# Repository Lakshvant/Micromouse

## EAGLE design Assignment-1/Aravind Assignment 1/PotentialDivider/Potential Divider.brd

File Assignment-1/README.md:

# Micromouse Assignment 1
Robotics Club , SNT ,  IITK 

All the mentees are requested to make a schematic file and a pcb file for these 4 circuits.
* Potential divider
* Astable multivibrator 
* Wheatstone bridge
* Diode as voltage regulator

## Submission Format
In the Assignment-1 folder of the repo make a folder in your name containing the 
files and make a pull request when your are done
 
### Note :
You will need to fork the repo before making any changes in it.\
Contact mentors if facing any issues.

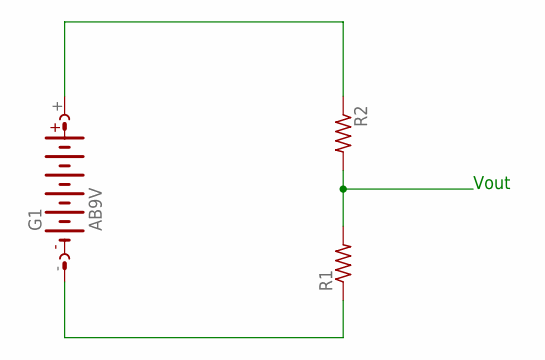
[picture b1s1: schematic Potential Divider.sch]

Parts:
G1: AB9V
R1, R2: R-US_R0805; R0805

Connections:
unnamed: G1.+, R2.1
unnamed: R1.2, R2.2
unnamed: G1.-, R1.1

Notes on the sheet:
Vout

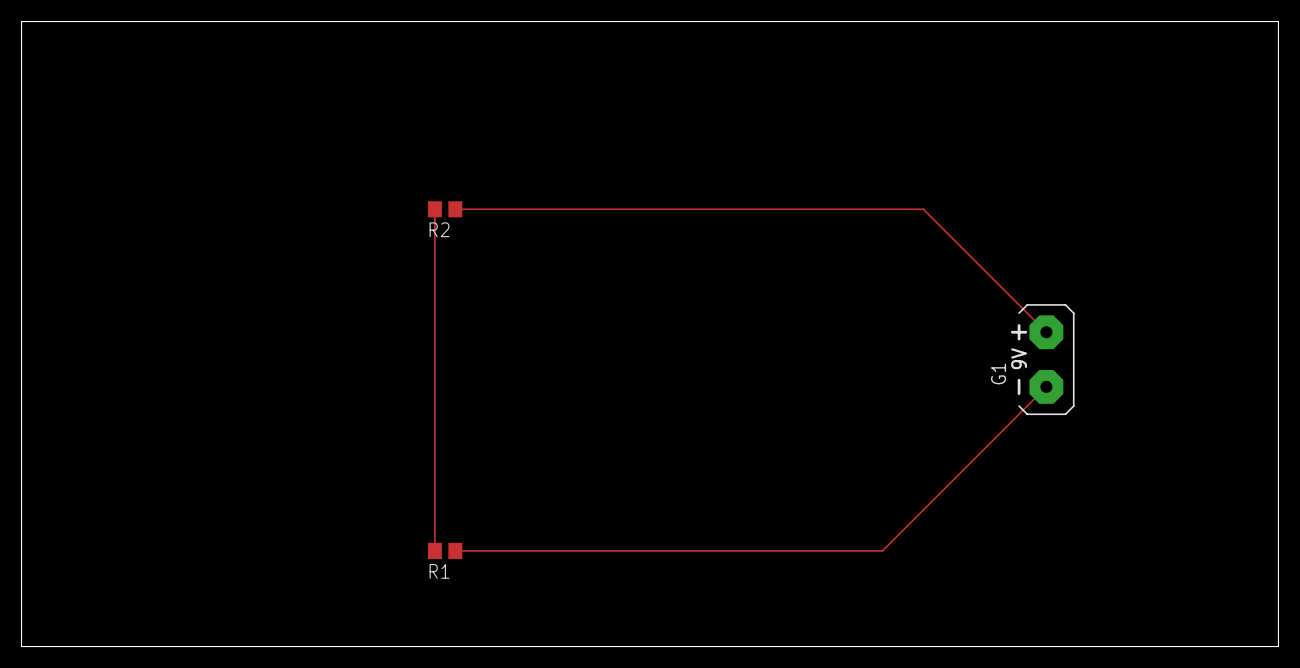
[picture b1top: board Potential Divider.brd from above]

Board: 2 copper layers, 116.8 x 58.1 mm, 3 parts (0 on the bottom side), 3 nets.

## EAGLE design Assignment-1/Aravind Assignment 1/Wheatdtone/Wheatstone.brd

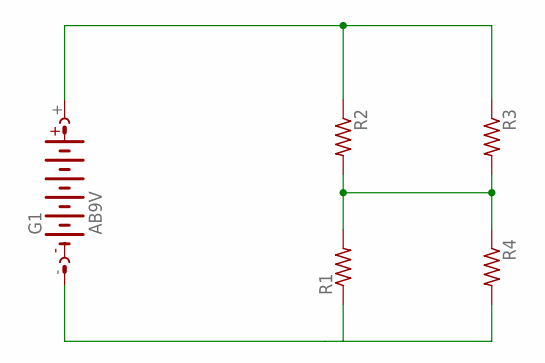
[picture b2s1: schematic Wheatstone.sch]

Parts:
G1: AB9V
R1, R2, R3, R4: R-US_R0805; R0805

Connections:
unnamed: G1.+, R2.1, R3.1
unnamed: R1.2, R2.2, R3.2, R4.1
unnamed: G1.-, R1.1, R4.2

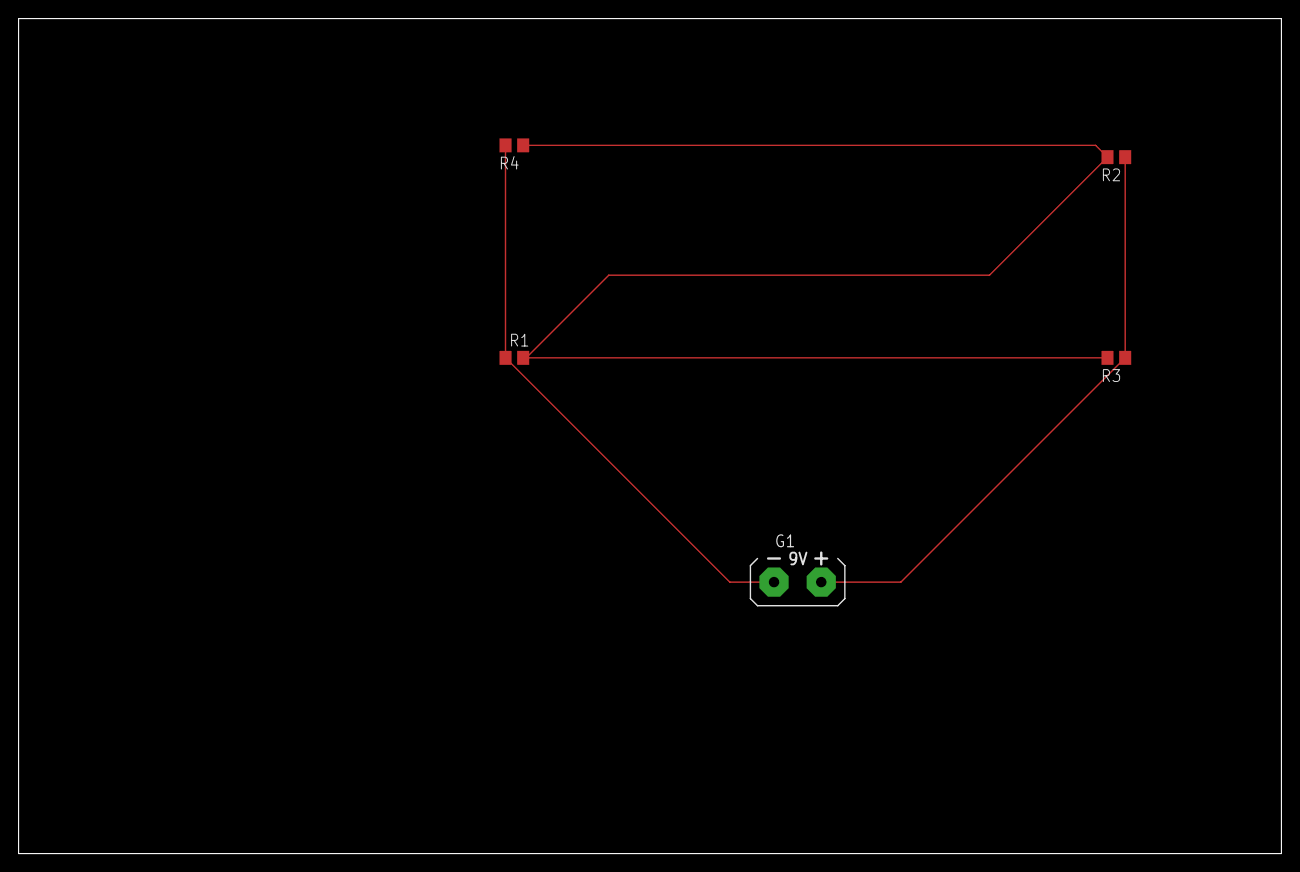
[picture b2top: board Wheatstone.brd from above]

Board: 2 copper layers, 135.9 x 89.8 mm, 5 parts (0 on the bottom side), 3 nets.

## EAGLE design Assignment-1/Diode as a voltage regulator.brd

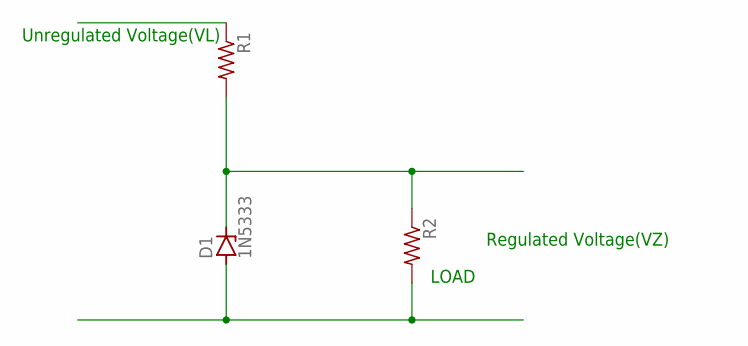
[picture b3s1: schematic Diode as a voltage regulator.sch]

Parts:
D1: 1N5333; C1702-15
R1, R2: R-US_R0805; R0805

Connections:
unnamed: D1.C, R1.2, R2.1
unnamed: D1.A, R2.2

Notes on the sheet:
Unregulated Voltage(VL)
Regulated Voltage(VZ)
LOAD

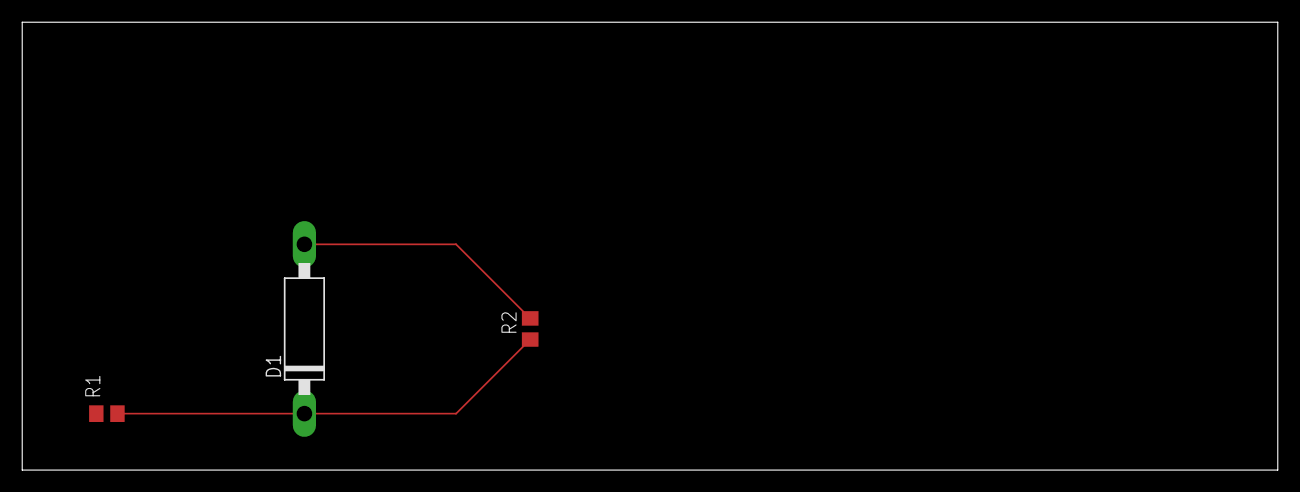
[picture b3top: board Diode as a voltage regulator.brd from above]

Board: 2 copper layers, 113.0 x 40.3 mm, 3 parts (0 on the bottom side), 2 nets.

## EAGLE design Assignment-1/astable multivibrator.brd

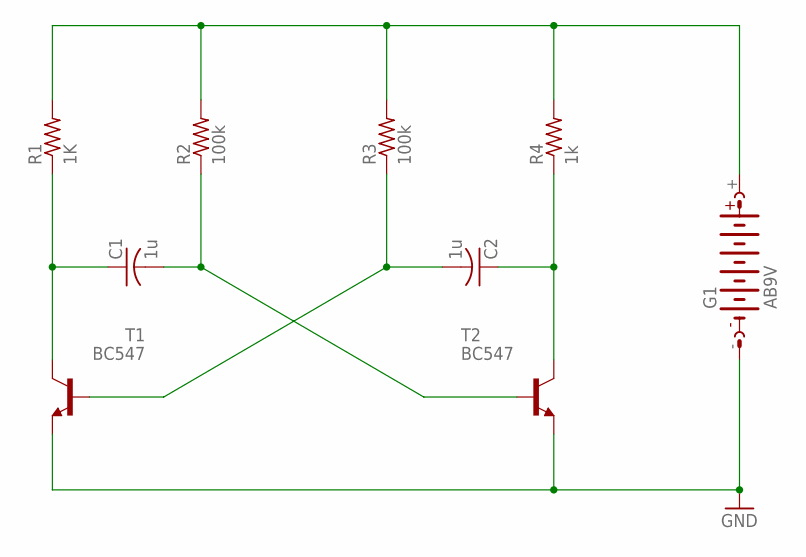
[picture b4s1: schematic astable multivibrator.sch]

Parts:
C1, C2: 1u; C0805
G1: AB9V
R1: 1K; R0805
R2, R3: 100k; R0805
R4: 1k; R0805
T1, T2: BC547; TO92

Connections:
GND: G1.-, T1.1 (E), T2.1 (E)
unnamed: G1.+, R1.2, R2.2, R3.2, R4.2
unnamed: C2.2, R3.1, T1.2 (B)
unnamed: C1.2, R2.1, T2.2 (B)
unnamed: C1.1, R1.1, T1.3 (C)
unnamed: C2.1, R4.1, T2.3 (C)

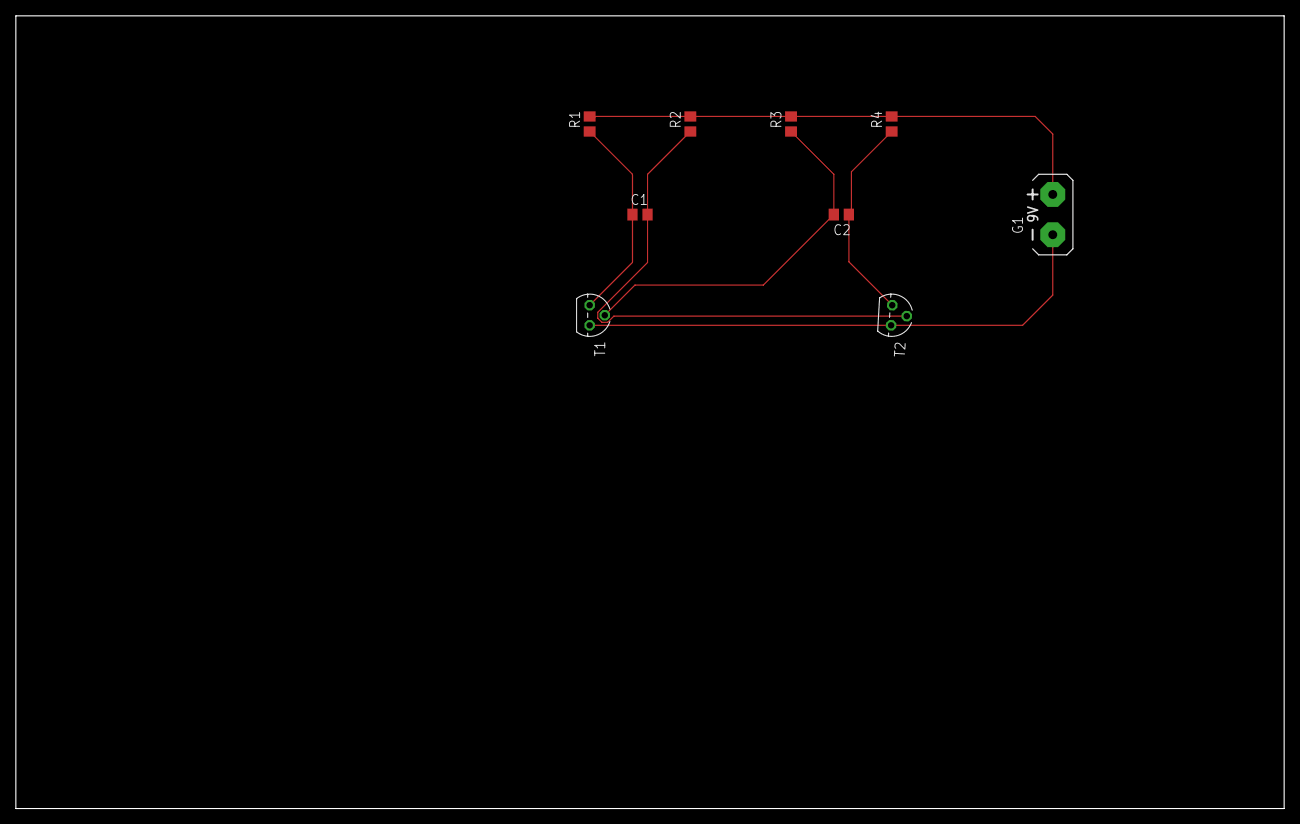
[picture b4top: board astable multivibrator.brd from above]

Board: 2 copper layers, 160.0 x 100.0 mm, 9 parts (0 on the bottom side), 6 nets.

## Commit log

2022-06-25 Create lakshvant
2022-06-25 Create roboproj1
2022-07-19 added testing codes
